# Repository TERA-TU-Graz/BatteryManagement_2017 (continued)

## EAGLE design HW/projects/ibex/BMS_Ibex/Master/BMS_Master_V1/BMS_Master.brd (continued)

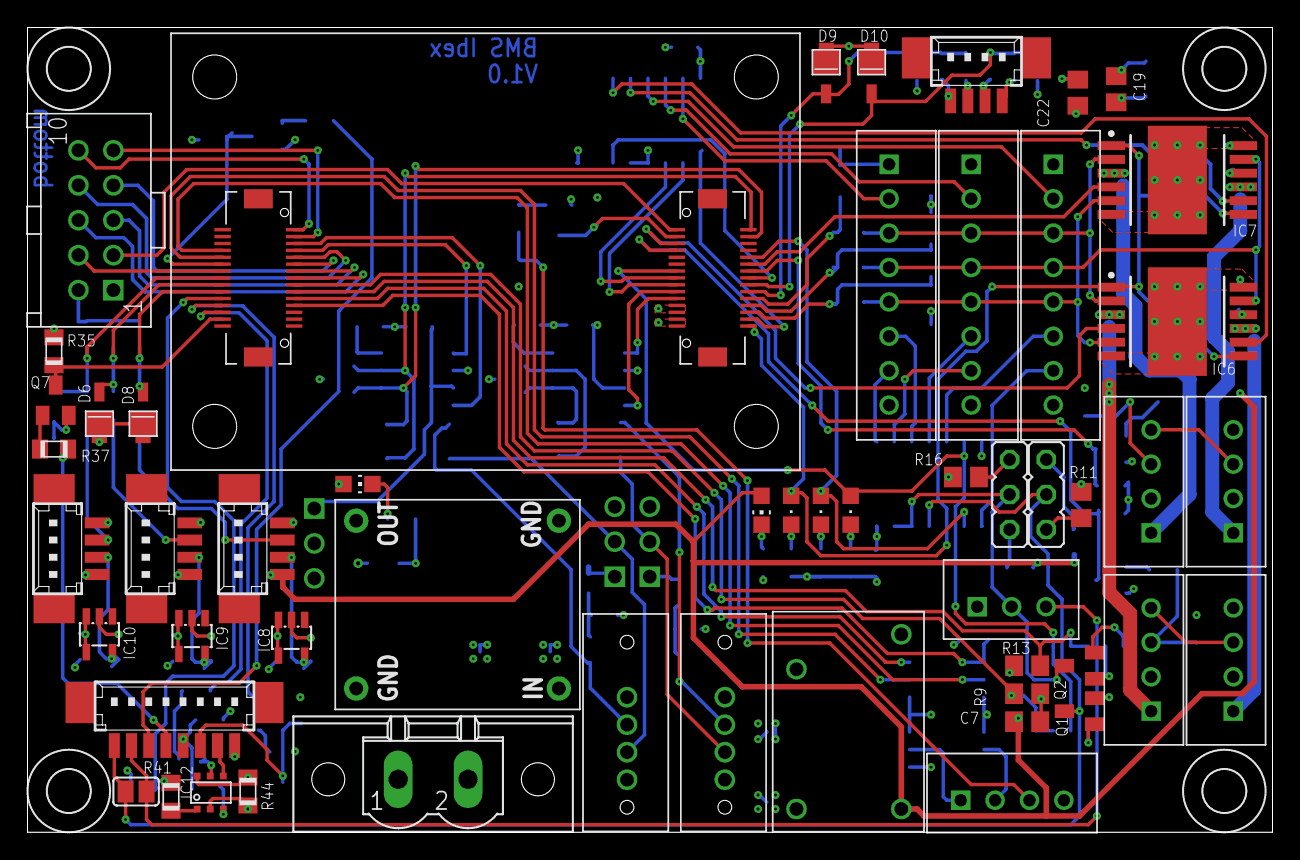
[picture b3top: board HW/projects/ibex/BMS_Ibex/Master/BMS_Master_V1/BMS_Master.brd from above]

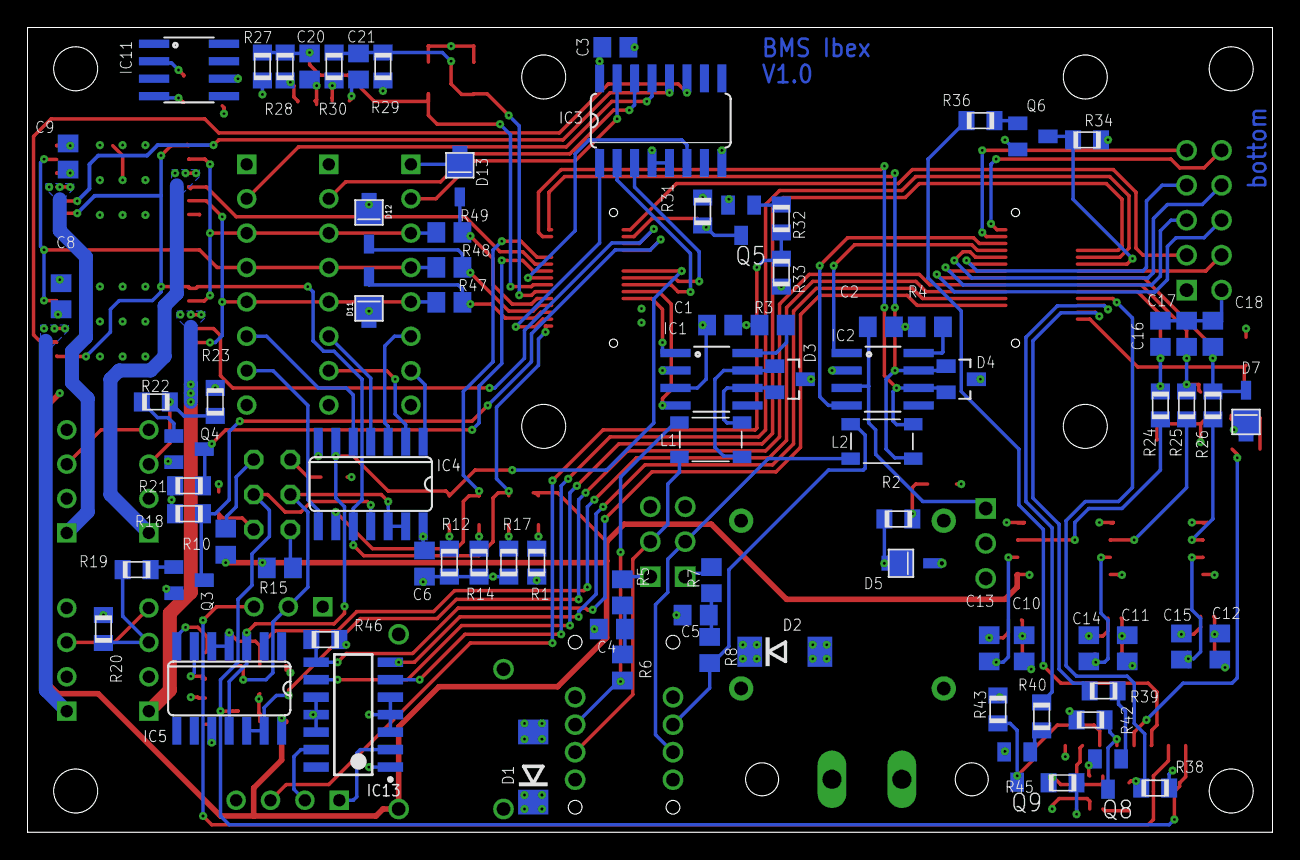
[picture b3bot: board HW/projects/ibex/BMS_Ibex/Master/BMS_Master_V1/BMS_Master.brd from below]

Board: 4 copper layers, 90.5 x 58.5 mm, 144 parts (84 on the bottom side), 125 nets.

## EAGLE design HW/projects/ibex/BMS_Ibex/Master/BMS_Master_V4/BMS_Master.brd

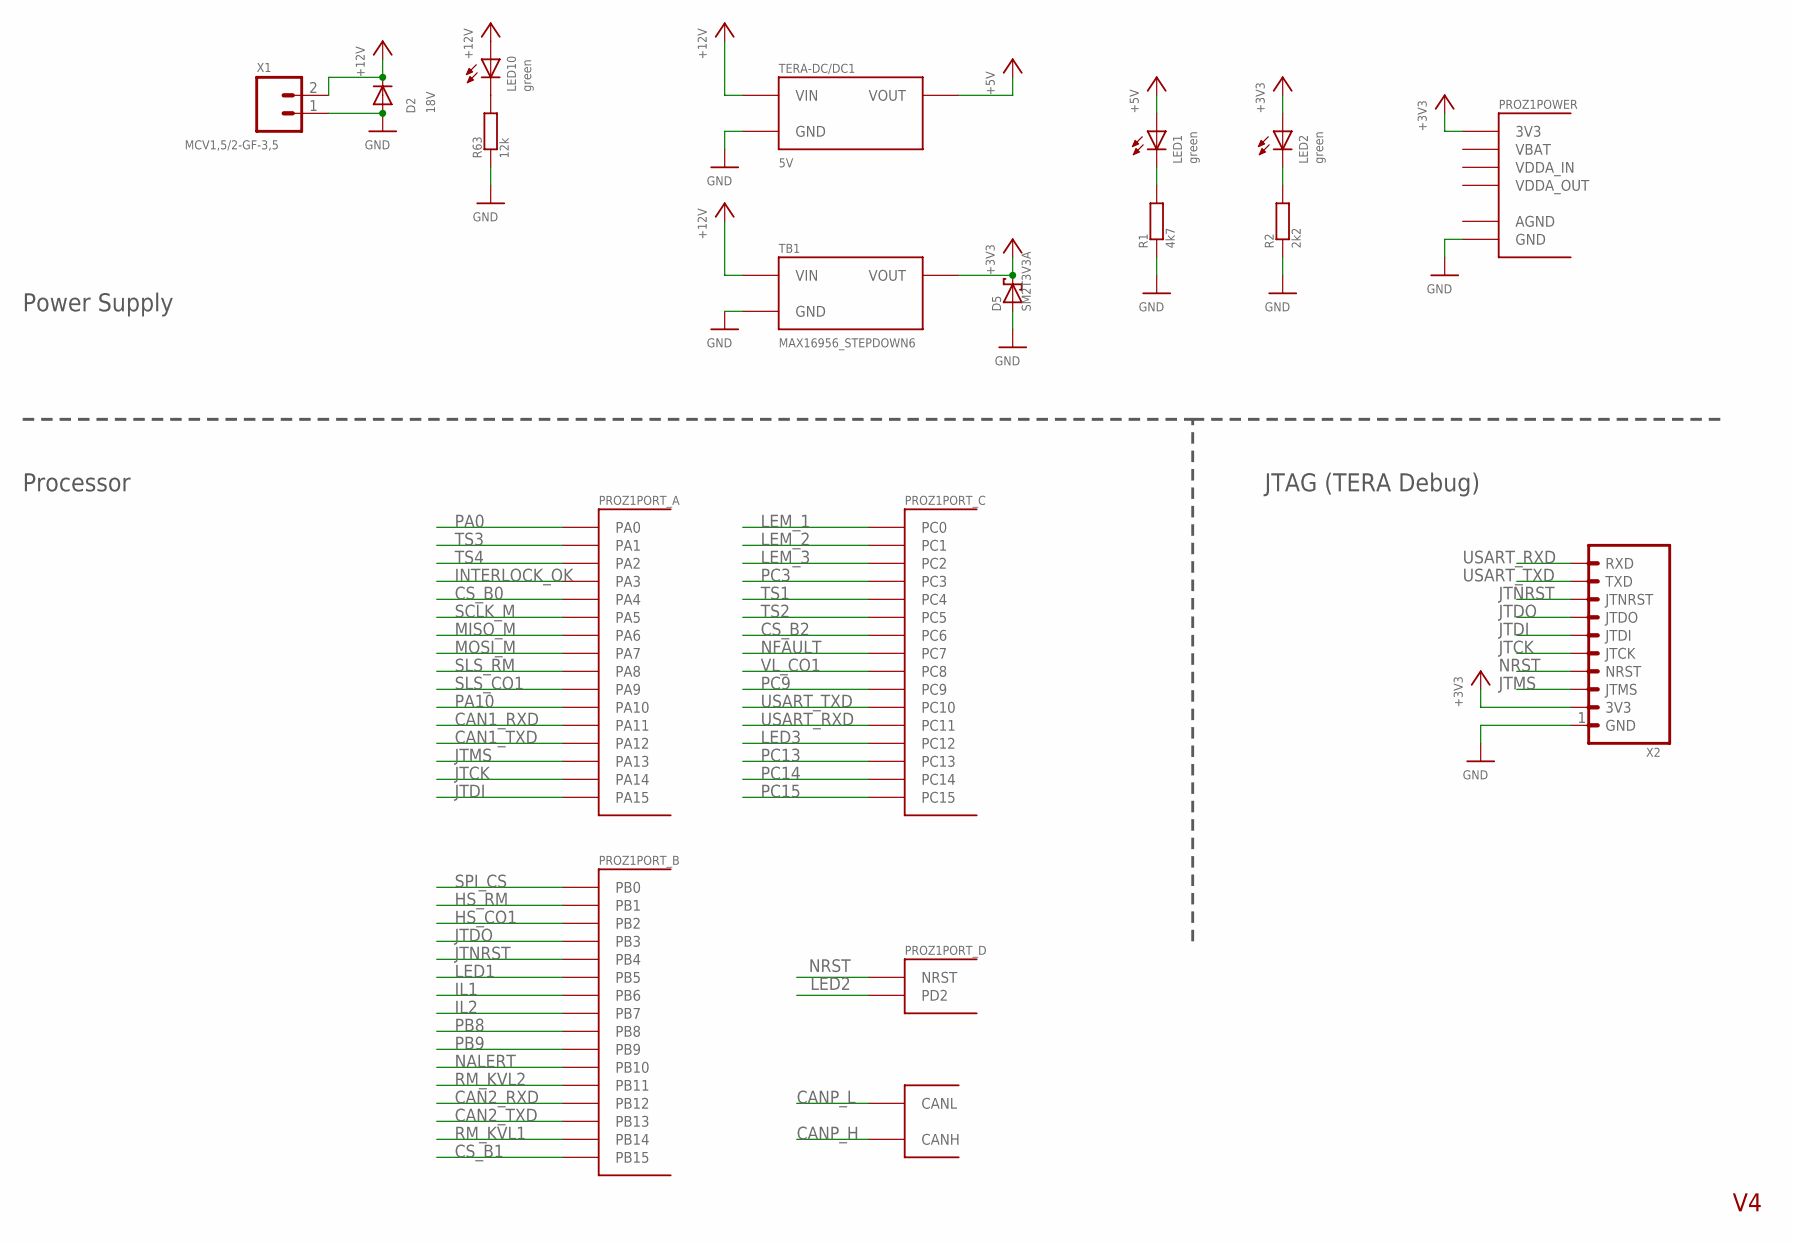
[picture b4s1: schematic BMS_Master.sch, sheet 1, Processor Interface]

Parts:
D2: 18V; DO214AA
D5: SM2T3V3A
LED1, LED2, LED10: green; CHIP-LED0805
PROZ1: STM32F4_PROZESSORBOARDRPZ; STM32F4_PROZESSORBOARD
R1: 4k7; R0805
R2: 2k2; R0805
R63: 12k; R0805
TB1: MAX16956_STEPDOWN6
TERA-DC/DC1: 5V; MAX5035_STEPDOWN3
X1: MCV1,5/2-GF-3,5
X2: TERA-PROG-DEBUG-10GERADE; 90130-1110

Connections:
+3V3: D5.P$2, LED2.A, PROZ1.45 (3V3), PROZ1.46 (3V3), TB1.VOUT, X2.2 (3V3); also elsewhere on the board
+5V: LED1.A, TERA-DC/DC1.VOUT; also elsewhere on the board
+12V: D2.C, LED10.A, TB1.VIN, TERA-DC/DC1.VIN, X1.2; also elsewhere on the board
CAN1_RXD: PROZ1.26 (PA11); also elsewhere on the board
CAN1_TXD: PROZ1.24 (PA12); also elsewhere on the board
CAN2_RXD: PROZ1.50 (PB12); also elsewhere on the board
CAN2_TXD: PROZ1.49 (PB13); also elsewhere on the board
CANP_H: PROZ1.31 (CANH); also elsewhere on the board
CANP_L: PROZ1.32 (CANL); also elsewhere on the board
CS_B0: PROZ1.43 (PA4); also elsewhere on the board
CS_B1: PROZ1.51 (PB15); also elsewhere on the board
CS_B2: PROZ1.52 (PC6); also elsewhere on the board
GND: D2.A, D5.P$1, D5.P$11, PROZ1.47 (GND), PROZ1.48 (GND), R1.1, R2.1, R63.1, TB1.GND, TB1.GND2 (GND), TERA-DC/DC1.GND@1 (GND), TERA-DC/DC1.GND@2 (GND), X1.1, X2.1 (GND); also elsewhere on the board
HS_CO1: PROZ1.36 (PB2); also elsewhere on the board
HS_RM: PROZ1.37 (PB1); also elsewhere on the board
IL1: PROZ1.14 (PB6); also elsewhere on the board
IL2: PROZ1.12 (PB7); also elsewhere on the board
INTERLOCK_OK: PROZ1.44 (PA3); also elsewhere on the board
JTCK: PROZ1.18 (PA14), X2.5 (JTCK)
JTDI: PROZ1.16 (PA15), X2.6 (JTDI)
JTDO: PROZ1.20 (PB3), X2.7 (JTDO)
JTMS: PROZ1.59 (PA13), X2.3 (JTMS)
JTNRST: PROZ1.22 (PB4), X2.8 (JTNRST)
LED1: PROZ1.25 (PB5)
LED2: PROZ1.27 (PD2)
LED3: PROZ1.29 (PC12)
LEM_1: PROZ1.15 (PC0); also elsewhere on the board
LEM_2: PROZ1.13 (PC1); also elsewhere on the board
LEM_3: PROZ1.11 (PC2); also elsewhere on the board
MISO_M: PROZ1.42 (PA6); also elsewhere on the board
MOSI_M: PROZ1.41 (PA7); also elsewhere on the board
unnamed: LED1.C, R1.2
unnamed: LED2.C, R2.2
unnamed: LED10.C, R63.2
NALERT: PROZ1.35 (PB10); also elsewhere on the board
NFAULT: PROZ1.53 (PC7); also elsewhere on the board
NRST: PROZ1.17 (NRST), X2.4 (NRST)
PA0: PROZ1.7 (PA0)
PA10: PROZ1.58 (PA10)
PB8: PROZ1.10 (PB8)
PB9: PROZ1.8 (PB9)
PC3: PROZ1.9 (PC3)
PC9: PROZ1.55 (PC9)
PC13: PROZ1.23 (PC13)
PC14: PROZ1.21 (PC14)
PC15: PROZ1.19 (PC15)
RM_KVL1: PROZ1.33 (PB14); also elsewhere on the board
RM_KVL2: PROZ1.34 (PB11); also elsewhere on the board
SCLK_M: PROZ1.60 (PA5); also elsewhere on the board
SLS_CO1: PROZ1.57 (PA9); also elsewhere on the board
SLS_RM: PROZ1.56 (PA8); also elsewhere on the board
SPI_CS: PROZ1.38 (PB0); also elsewhere on the board
TS1: PROZ1.40 (PC4); also elsewhere on the board
TS2: PROZ1.39 (PC5); also elsewhere on the board
TS3: PROZ1.5 (PA1); also elsewhere on the board
TS4: PROZ1.3 (PA2); also elsewhere on the board
USART_RXD: PROZ1.30 (PC11), X2.10 (RXD)
USART_TXD: PROZ1.28 (PC10), X2.9 (TXD)
VL_CO1: PROZ1.54 (PC8); also elsewhere on the board

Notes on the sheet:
Power Supply
Processor
JTAG (TERA Debug)

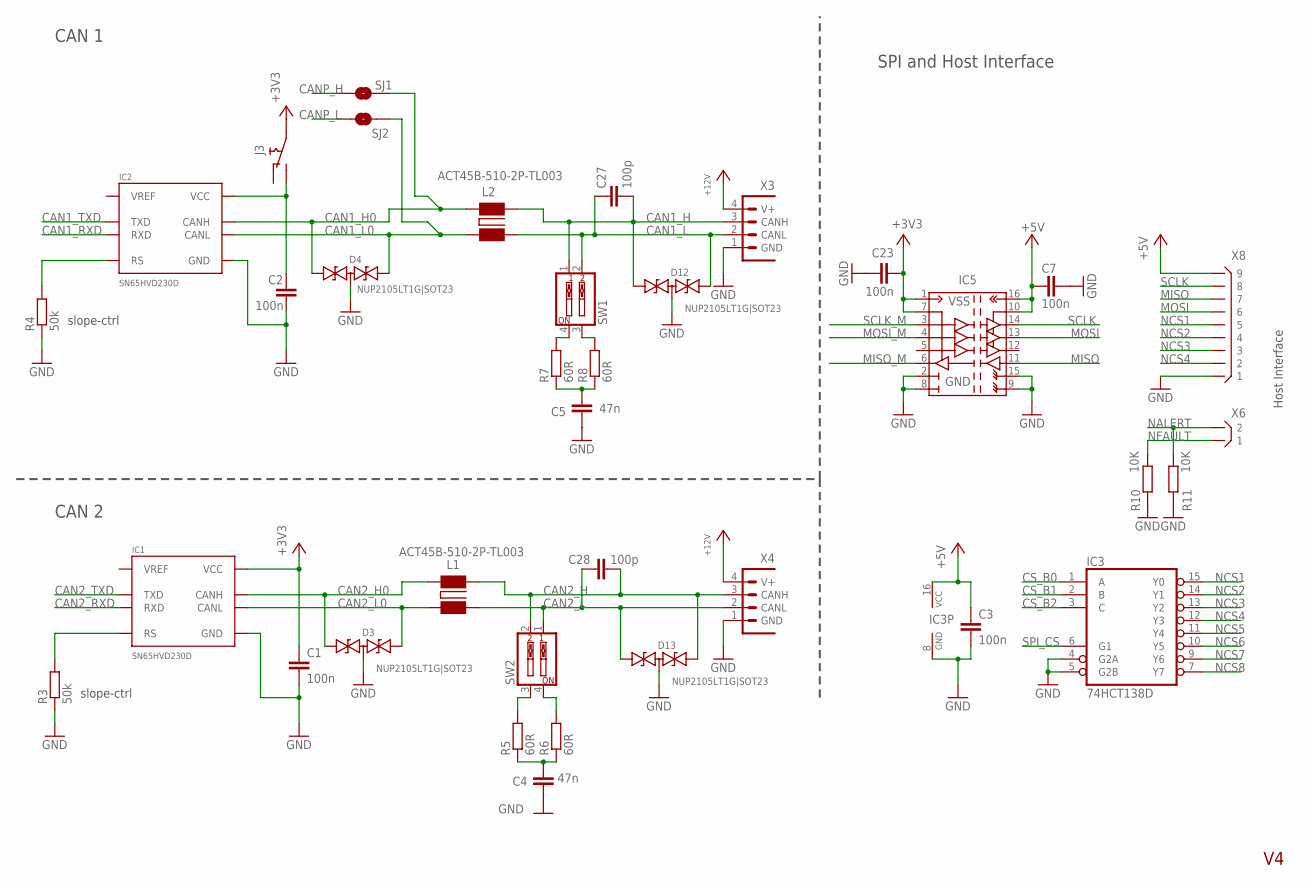
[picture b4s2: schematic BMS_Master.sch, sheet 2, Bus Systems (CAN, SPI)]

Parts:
C1, C2, C3: 100n; C0805
C4, C5: 47n; C0603
C7, C23: 100n; C0603
C27, C28: 100p; C0603
D3, D4, D12, D13: NUP2105LT1G|SOT23; SOT23
IC1, IC2: SN65HVD230D; SO08
IC3: 74HCT138D; SO16
IC5: ISO7241; R-PDSO-G16
J3: JUMPER_SWITCHS; J_OR_S
L1, L2: ACT45B-510-2P-TL003; ACT45B
R3, R4: 50k; R0805
R5, R6, R7, R8: 60R; R0603
R10, R11: 10K; R0603
SJ1, SJ2: SOLDERJUMPERNO; SJ_2S-NO
SW1, SW2: DIP_SWITCH_DIP2; DIPSWITCH-02
X3, X4: CIOC_4-1-FV-A_CAN-BELEGUNG; CIOC_4-1-FV
X6: B2B-XH
X8: B9B-XH

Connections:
+3V3: C1.1, C23.2, IC1.3 (VCC), IC5.1 (VCC1), IC5.7 (EN1), J3.P$1; also elsewhere on the board
+5V: C3.1, C7.2, IC3.16 (VCC), IC5.10 (EN2), IC5.16 (VCC2), X8.P$9 (9); also elsewhere on the board
+12V: X3.4 (V+), X4.4 (V+); also elsewhere on the board
CAN1_H: C27.2, D12.1, L2.P$3 (3), SW1.1, X3.3 (CANH)
CAN1_H0: D4.1, IC2.7 (CANH), L2.P$4 (4), SJ1.1
CAN1_L: C27.1, D12.2, L2.P$1 (1), SW1.2, X3.2 (CANL)
CAN1_L0: D4.2, IC2.6 (CANL), L2.P$2 (2), SJ2.1
CAN1_RXD: IC2.4 (RXD); also elsewhere on the board
CAN1_TXD: IC2.1 (TXD); also elsewhere on the board
CAN2_H: C28.2, D13.2, L1.P$3 (3), SW2.2, X4.3 (CANH)
CAN2_H0: D3.1, IC1.7 (CANH), L1.P$4 (4)
CAN2_L: C28.1, D13.1, L1.P$1 (1), SW2.1, X4.2 (CANL)
CAN2_L0: D3.2, IC1.6 (CANL), L1.P$2 (2)
CAN2_RXD: IC1.4 (RXD); also elsewhere on the board
CAN2_TXD: IC1.1 (TXD); also elsewhere on the board
CANP_H: SJ1.2; also elsewhere on the board
CANP_L: SJ2.2; also elsewhere on the board
CS_B0: IC3.1 (A); also elsewhere on the board
CS_B1: IC3.2 (B); also elsewhere on the board
CS_B2: IC3.3 (C); also elsewhere on the board
GND: C1.2, C2.2, C3.2, C4.2, C5.2, C7.1, C23.1, D3.3, D4.3, D12.3, D13.3, IC1.2 (GND), IC2.2 (GND), IC3.4 (G2A), IC3.5 (G2B), IC3.8 (GND), IC5.2 (GND11), IC5.8 (GND12), IC5.9 (GND22), IC5.15 (GND21), R3.1, R4.1, R10.1, R11.1, X3.1 (GND), X4.1 (GND), X8.P$1 (1); also elsewhere on the board
MISO: IC5.11 (IN_D), X8.P$7 (7); also elsewhere on the board
MISO_M: IC5.6 (OUT_D); also elsewhere on the board
MOSI: IC5.13 (OUT_B), X8.P$6 (6); also elsewhere on the board
MOSI_M: IC5.4 (IN_B); also elsewhere on the board
unnamed: C5.1, R7.1, R8.1
unnamed: C2.1, IC2.3 (VCC), J3.P$2
unnamed: IC2.8 (RS), R4.2
unnamed: C4.1, R5.1, R6.1
unnamed: R7.2, SW1.4
unnamed: IC1.8 (RS), R3.2
unnamed: R5.2, SW2.3
unnamed: R6.2, SW2.4
unnamed: R8.2, SW1.3
NALERT: R11.2, X6.P$2 (2); also elsewhere on the board
NCS1: IC3.15 (Y0), X8.P$5 (5)
NCS2: IC3.14 (Y1), X8.P$4 (4)
NCS3: IC3.13 (Y2), X8.P$3 (3)
NCS4: IC3.12 (Y3), X8.P$2 (2)
NCS5: IC3.11 (Y4)
NCS6: IC3.10 (Y5); also elsewhere on the board
NCS7: IC3.9 (Y6); also elsewhere on the board
NCS8: IC3.7 (Y7); also elsewhere on the board
NFAULT: R10.2, X6.P$1 (1); also elsewhere on the board
SCLK: IC5.14 (OUT_A), X8.P$8 (8); also elsewhere on the board
SCLK_M: IC5.3 (IN_A); also elsewhere on the board
SPI_CS: IC3.6 (G1); also elsewhere on the board

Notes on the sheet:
slope-ctrl
Host Interface
CAN 1
CAN 2
SPI and Host Interface

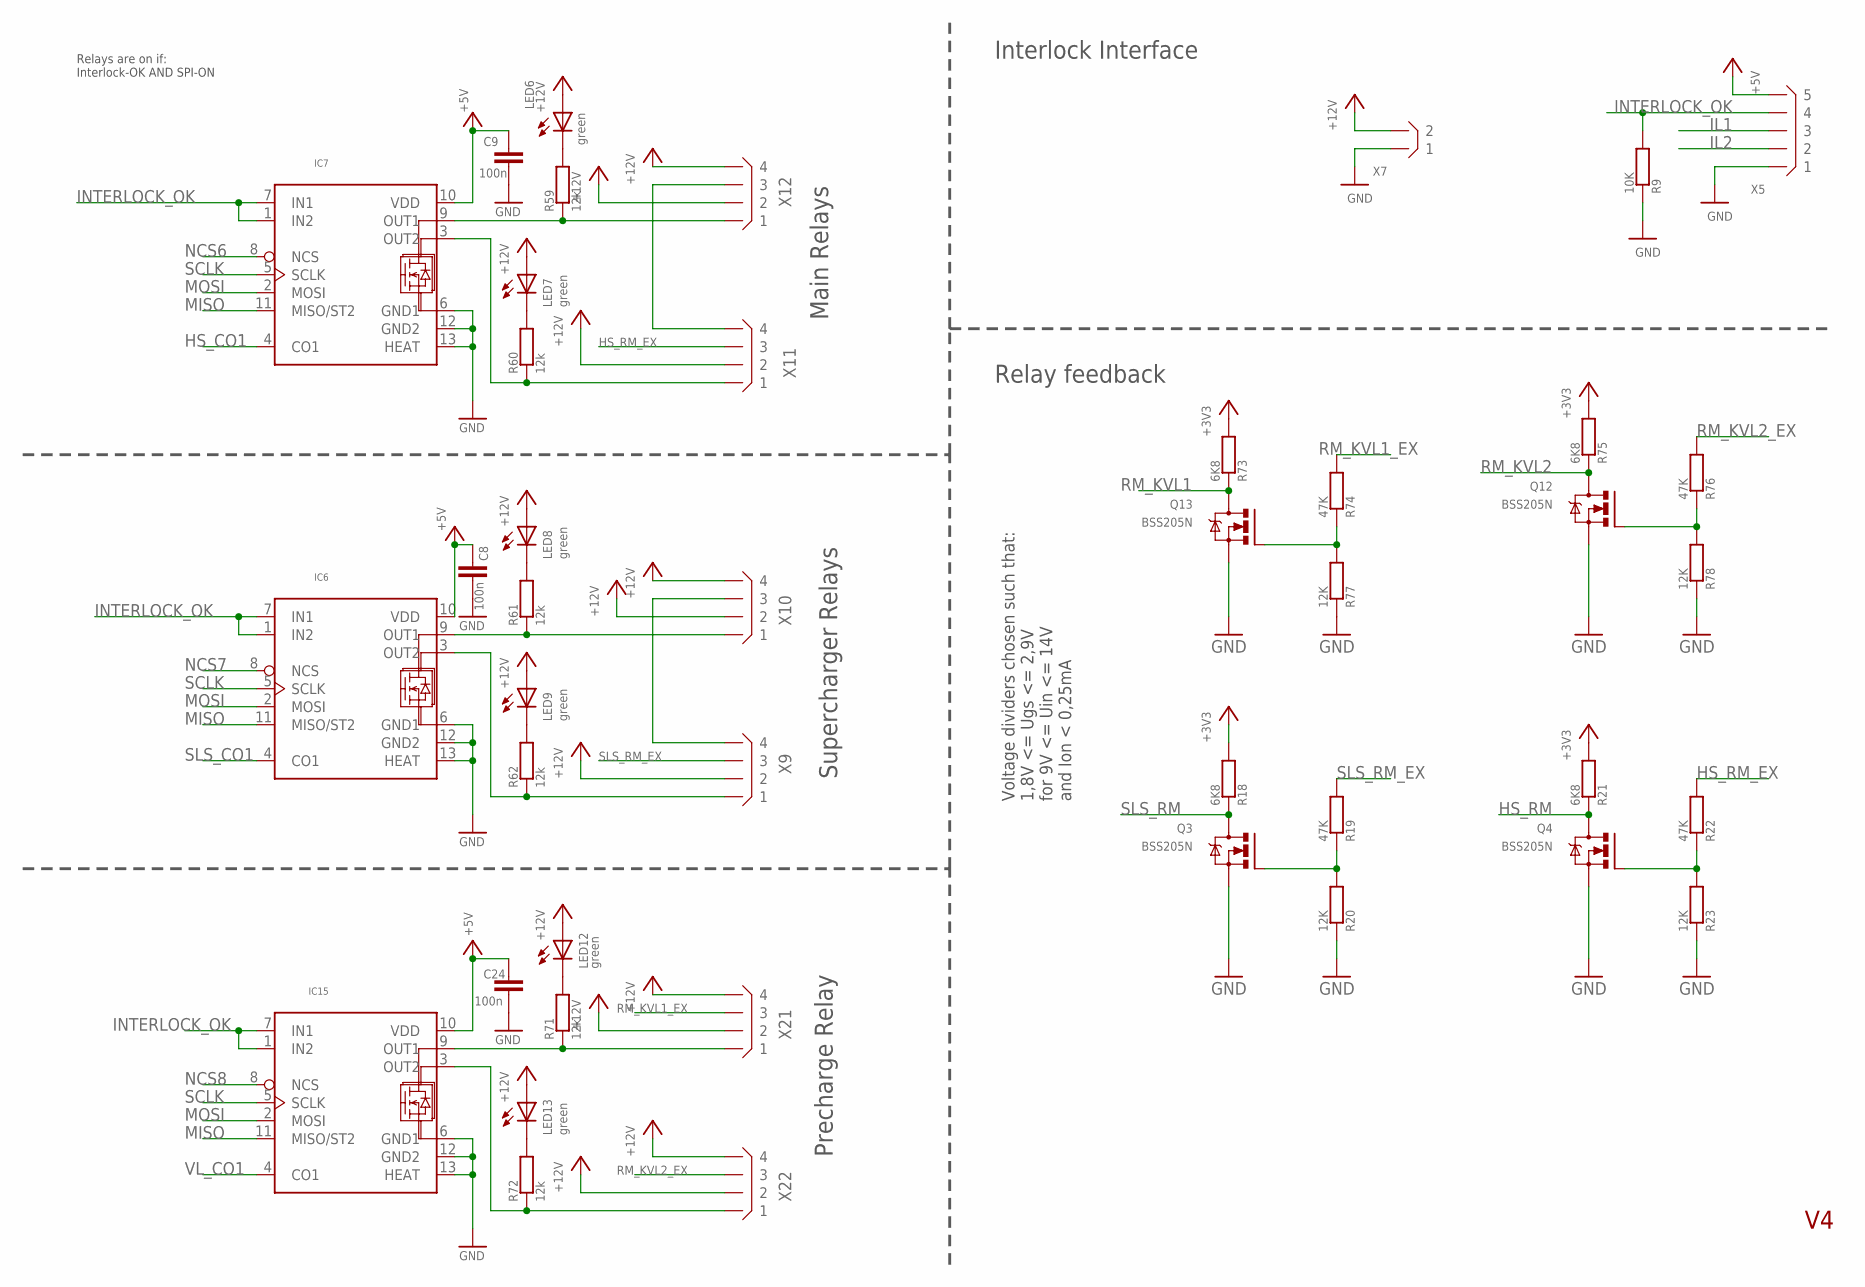
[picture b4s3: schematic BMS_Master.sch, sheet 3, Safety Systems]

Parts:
C8, C9, C24: 100n; C0603
IC6, IC7, IC15: TLE8102SGN; INF-PG-DSO-12-11_N_1PRIMARY
LED6, LED7, LED8, LED9, LED12, LED13: green; CHIP-LED0805
Q3, Q4, Q12, Q13: BSS205N; SOT23
R9: 10K; R0805
R18, R21: 6K8; R0603
R19, R22, R74, R76: 47K; R0805
R20, R23, R77, R78: 12K; R0805
R59, R60, R61, R62, R71, R72: 12k; R0805
R73, R75: 6K8; R0805
X5: B5B-XH
X7: B2B-XH
X9, X10, X11, X12, X21, X22: B4B-XH

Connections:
+3V3: R18.2, R21.2, R73.2, R75.2; also elsewhere on the board
+5V: C8.1, C9.1, C24.1, IC6.10 (VDD), IC7.10 (VDD), IC15.10 (VDD), X5.P$5 (5); also elsewhere on the board
+12V: LED6.A, LED7.A, LED8.A, LED9.A, LED12.A, LED13.A, X7.P$2 (2), X9.P$2 (2), X10.P$2 (2), X10.P$4 (4), X11.P$2 (2), X12.P$2 (2), X12.P$4 (4), X21.P$2 (2), X21.P$4 (4), X22.P$2 (2), X22.P$4 (4); also elsewhere on the board
GND: C8.2, C9.2, C24.2, IC6.6 (GND1), IC6.12 (GND2), IC6.13 (HEAT), IC7.6 (GND1), IC7.12 (GND2), IC7.13 (HEAT), IC15.6 (GND1), IC15.12 (GND2), IC15.13 (HEAT), Q3.2 (S), Q4.2 (S), Q12.2 (S), Q13.2 (S), R9.1, R20.1, R23.1, R77.1, R78.1, X5.P$1 (1), X7.P$1 (1); also elsewhere on the board
HS_CO1: IC7.4 (CO1); also elsewhere on the board
HS_RM: Q4.3 (D), R21.1; also elsewhere on the board
HS_RM_EX: R22.2, X11.P$3 (3)
IL1: X5.P$3 (3); also elsewhere on the board
IL2: X5.P$2 (2); also elsewhere on the board
INTERLOCK_OK: IC6.1 (IN2), IC6.7 (IN1), IC7.1 (IN2), IC7.7 (IN1), IC15.1 (IN2), IC15.7 (IN1), R9.2, X5.P$4 (4); also elsewhere on the board
MISO: IC6.11 (MISO/ST2), IC7.11 (MISO/ST2), IC15.11 (MISO/ST2); also elsewhere on the board
MOSI: IC6.2 (MOSI), IC7.2 (MOSI), IC15.2 (MOSI); also elsewhere on the board
unnamed: X9.P$4 (4), X10.P$3 (3)
unnamed: IC7.3 (OUT2), R60.1, X11.P$1 (1)
unnamed: IC6.9 (OUT1), R61.1, X10.P$1 (1)
unnamed: X11.P$4 (4), X12.P$3 (3)
unnamed: IC6.3 (OUT2), R62.1, X9.P$1 (1)
unnamed: IC7.9 (OUT1), R59.1, X12.P$1 (1)
unnamed: Q13.1 (G), R74.1, R77.2
unnamed: Q3.1 (G), R19.1, R20.2
unnamed: Q4.1 (G), R22.1, R23.2
unnamed: LED6.C, R59.2
unnamed: LED7.C, R60.2
unnamed: LED8.C, R61.2
unnamed: LED9.C, R62.2
unnamed: IC15.3 (OUT2), R72.1, X22.P$1 (1)
unnamed: IC15.9 (OUT1), R71.1, X21.P$1 (1)
unnamed: LED12.C, R71.2
unnamed: LED13.C, R72.2
unnamed: Q12.1 (G), R76.1, R78.2
NCS6: IC7.8 (NCS); also elsewhere on the board
NCS7: IC6.8 (NCS); also elsewhere on the board
NCS8: IC15.8 (NCS); also elsewhere on the board
RM_KVL1: Q13.3 (D), R73.1; also elsewhere on the board
RM_KVL1_EX: R74.2, X21.P$3 (3)
RM_KVL2: Q12.3 (D), R75.1; also elsewhere on the board
RM_KVL2_EX: R76.2, X22.P$3 (3)
SCLK: IC6.5 (SCLK), IC7.5 (SCLK), IC15.5 (SCLK); also elsewhere on the board
SLS_CO1: IC6.4 (CO1); also elsewhere on the board
SLS_RM: Q3.3 (D), R18.1; also elsewhere on the board
SLS_RM_EX: R19.2, X9.P$3 (3)
VL_CO1: IC15.4 (CO1); also elsewhere on the board

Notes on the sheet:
Main Relays
Supercharger Relays
Precharge Relay
Voltage dividers chosen such that: 1,8V <= Ugs <= 2,9V for 9V <= Uin <= 14V and Ion < 0,25mA
Relay feedback
Interlock Interface
Relays are on if: Interlock-OK AND SPI-ON

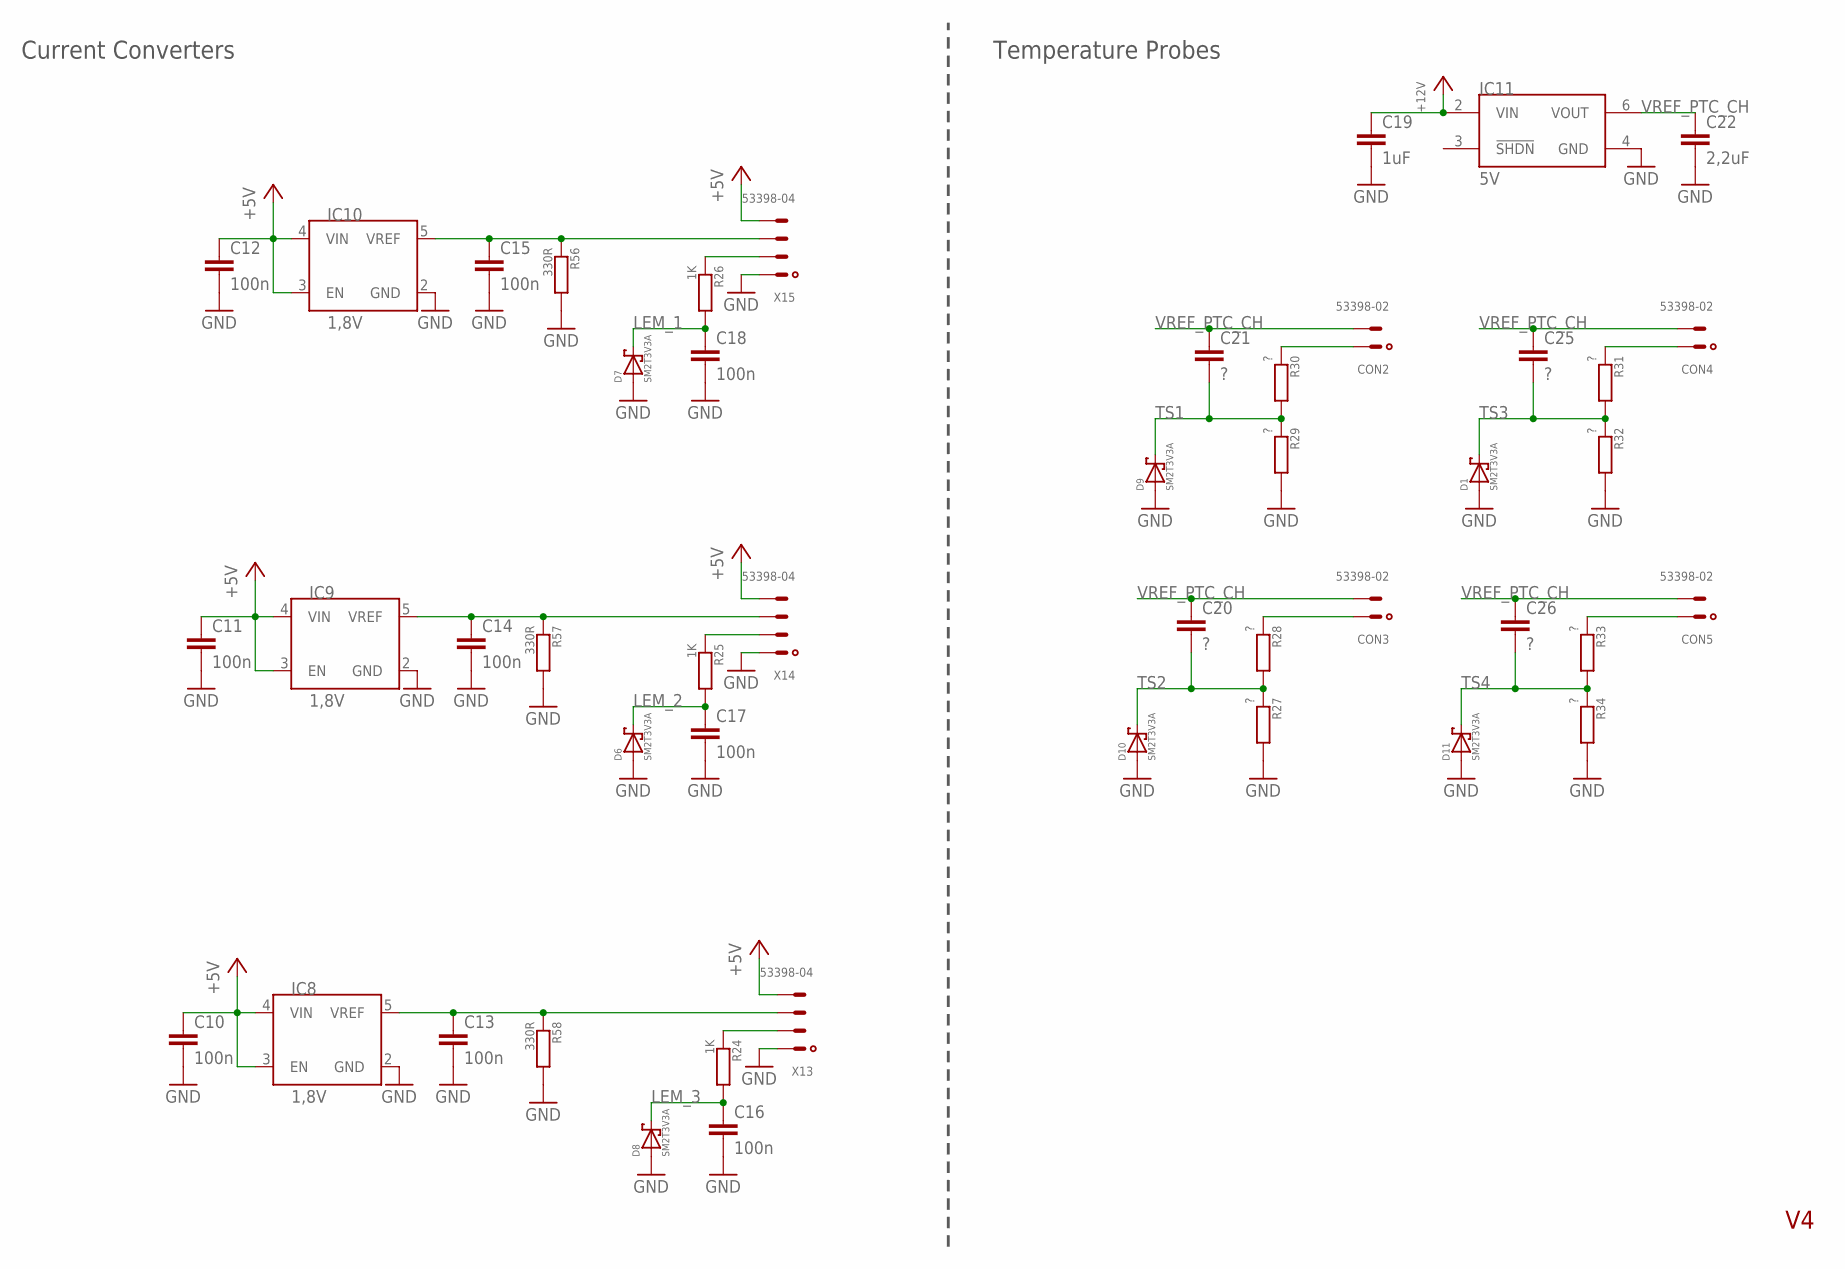
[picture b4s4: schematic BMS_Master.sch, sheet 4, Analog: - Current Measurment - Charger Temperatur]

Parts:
C10, C11, C12, C13, C14, C15, C16, C17, C18: 100n; C0805
C19: 1uF; C0805
C20, C21, C25, C26: ?; C0603
C22: 2,2uF; C0805
CON2, CON3, CON4, CON5: 53398-02
D1, D6, D7, D8, D9, D10, D11: SM2T3V3A
IC8, IC9, IC10: 1,8V; SOT23-5L
IC11: 5V; SO08
R24, R25, R26: 1K; R0805
R27, R28, R29, R30, R31, R32, R33, R34: ?; R0603
R56, R57, R58: 330R; R0805
X13, X14, X15: 53398-04

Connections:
+5V: C10.1, C11.1, C12.1, IC8.3 (EN), IC8.4 (VIN), IC9.3 (EN), IC9.4 (VIN), IC10.3 (EN), IC10.4 (VIN), X13.4, X14.4, X15.4; also elsewhere on the board
+12V: C19.1, IC11.2 (VIN); also elsewhere on the board
GND: C10.2, C11.2, C12.2, C13.2, C14.2, C15.2, C16.2, C17.2, C18.2, C19.2, C22.2, D1.P$1, D1.P$11, D6.P$1, D6.P$11, D7.P$1, D7.P$11, D8.P$1, D8.P$11, D9.P$1, D9.P$11, D10.P$1, D10.P$11, D11.P$1, D11.P$11, IC8.2 (GND), IC9.2 (GND), IC10.2 (GND), IC11.4 (GND), R27.2, R29.2, R32.2, R34.2, R56.2, R57.2, R58.2, X13.1, X14.1, X15.1; also elsewhere on the board
LEM_1: C18.1, D7.P$2, R26.2; also elsewhere on the board
LEM_2: C17.1, D6.P$2, R25.2; also elsewhere on the board
LEM_3: C16.1, D8.P$2, R24.2; also elsewhere on the board
unnamed: C13.1, IC8.5 (VREF), R58.1, X13.3
unnamed: R26.1, X15.2
unnamed: C14.1, IC9.5 (VREF), R57.1, X14.3
unnamed: CON4.1, R31.1
unnamed: CON5.1, R33.1
unnamed: CON2.1, R30.1
unnamed: R25.1, X14.2
unnamed: C15.1, IC10.5 (VREF), R56.1, X15.3
unnamed: R24.1, X13.2
unnamed: CON3.1, R28.1
TS1: C21.2, D9.P$2, R29.1, R30.2; also elsewhere on the board
TS2: C20.2, D10.P$2, R27.1, R28.2; also elsewhere on the board
TS3: C25.2, D1.P$2, R31.2, R32.1; also elsewhere on the board
TS4: C26.2, D11.P$2, R33.2, R34.1; also elsewhere on the board
VREF_PTC_CH: C20.1, C21.1, C22.1, C25.1, C26.1, CON2.2, CON3.2, CON4.2, CON5.2, IC11.6 (VOUT)

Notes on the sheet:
Temperature Probes
Current Converters

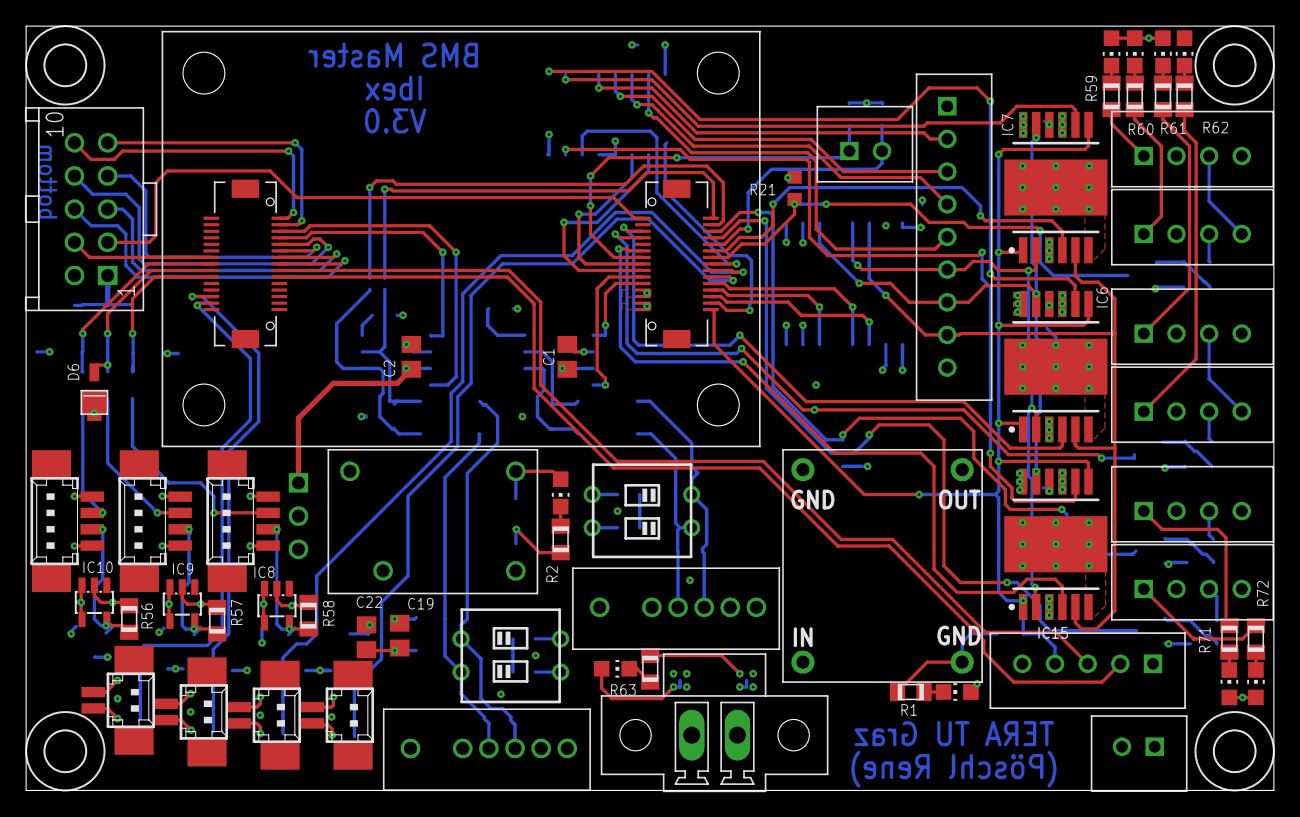
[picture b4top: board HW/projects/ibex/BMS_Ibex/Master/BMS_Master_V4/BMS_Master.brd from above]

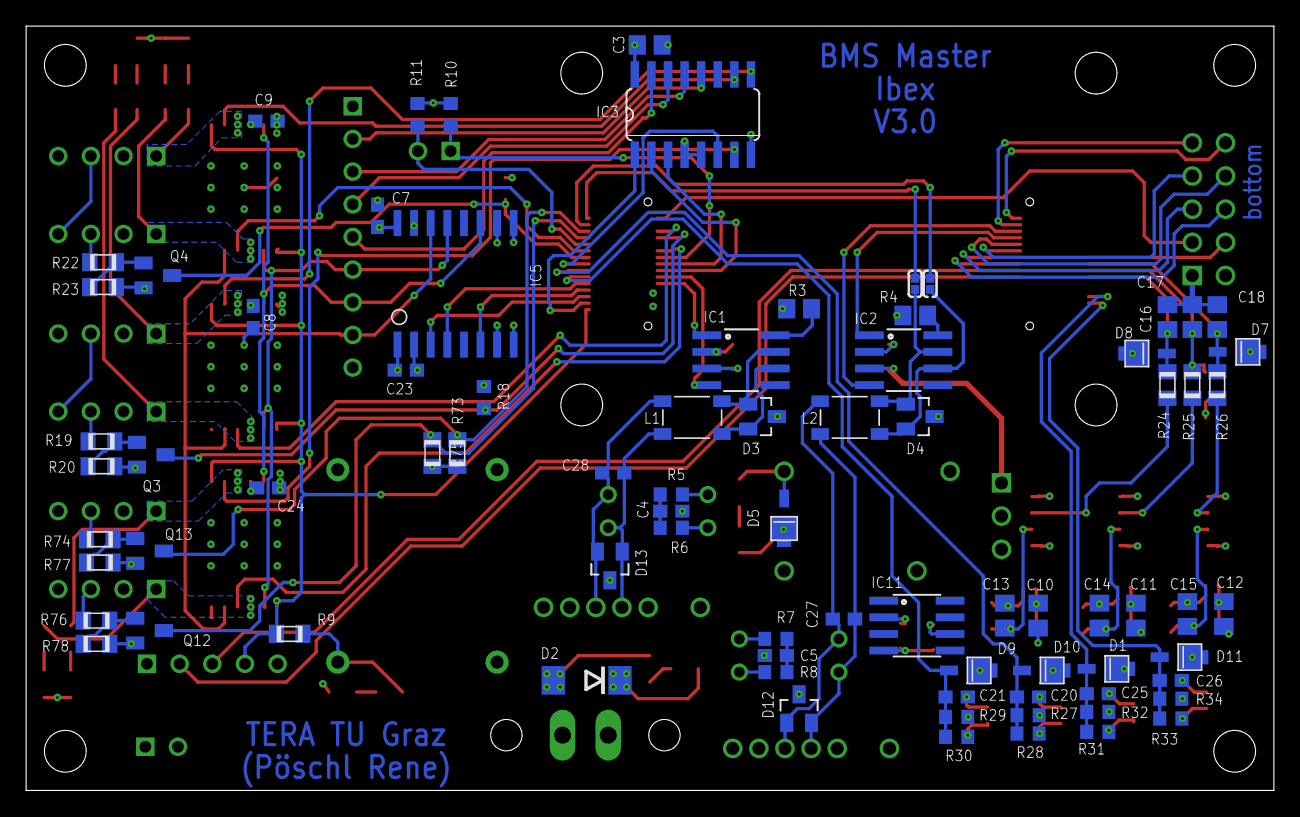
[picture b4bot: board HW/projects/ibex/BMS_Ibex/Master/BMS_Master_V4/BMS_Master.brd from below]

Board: 4 copper layers, 95.5 x 58.5 mm, 143 parts (79 on the bottom side), 107 nets.

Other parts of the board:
H1, H2, H3, H4: MOUNT-HOLE3.2; 3,2
